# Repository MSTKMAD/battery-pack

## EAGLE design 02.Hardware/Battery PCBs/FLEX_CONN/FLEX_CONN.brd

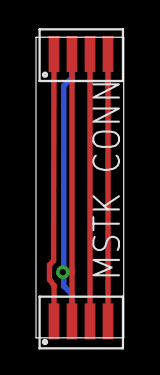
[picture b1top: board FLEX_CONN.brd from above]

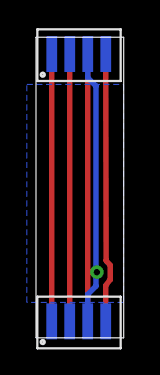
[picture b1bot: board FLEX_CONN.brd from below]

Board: 2 copper layers, 4.9 x 16.7 mm, 4 parts (2 on the bottom side), 4 nets.

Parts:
U$1, U$2, U$3, U$4: FLEX4

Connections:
GND: U$1.2, U$2.2, U$3.3, U$4.3
unnamed: U$1.1, U$2.1
unnamed: U$1.3, U$2.3
unnamed: U$1.4, U$2.4

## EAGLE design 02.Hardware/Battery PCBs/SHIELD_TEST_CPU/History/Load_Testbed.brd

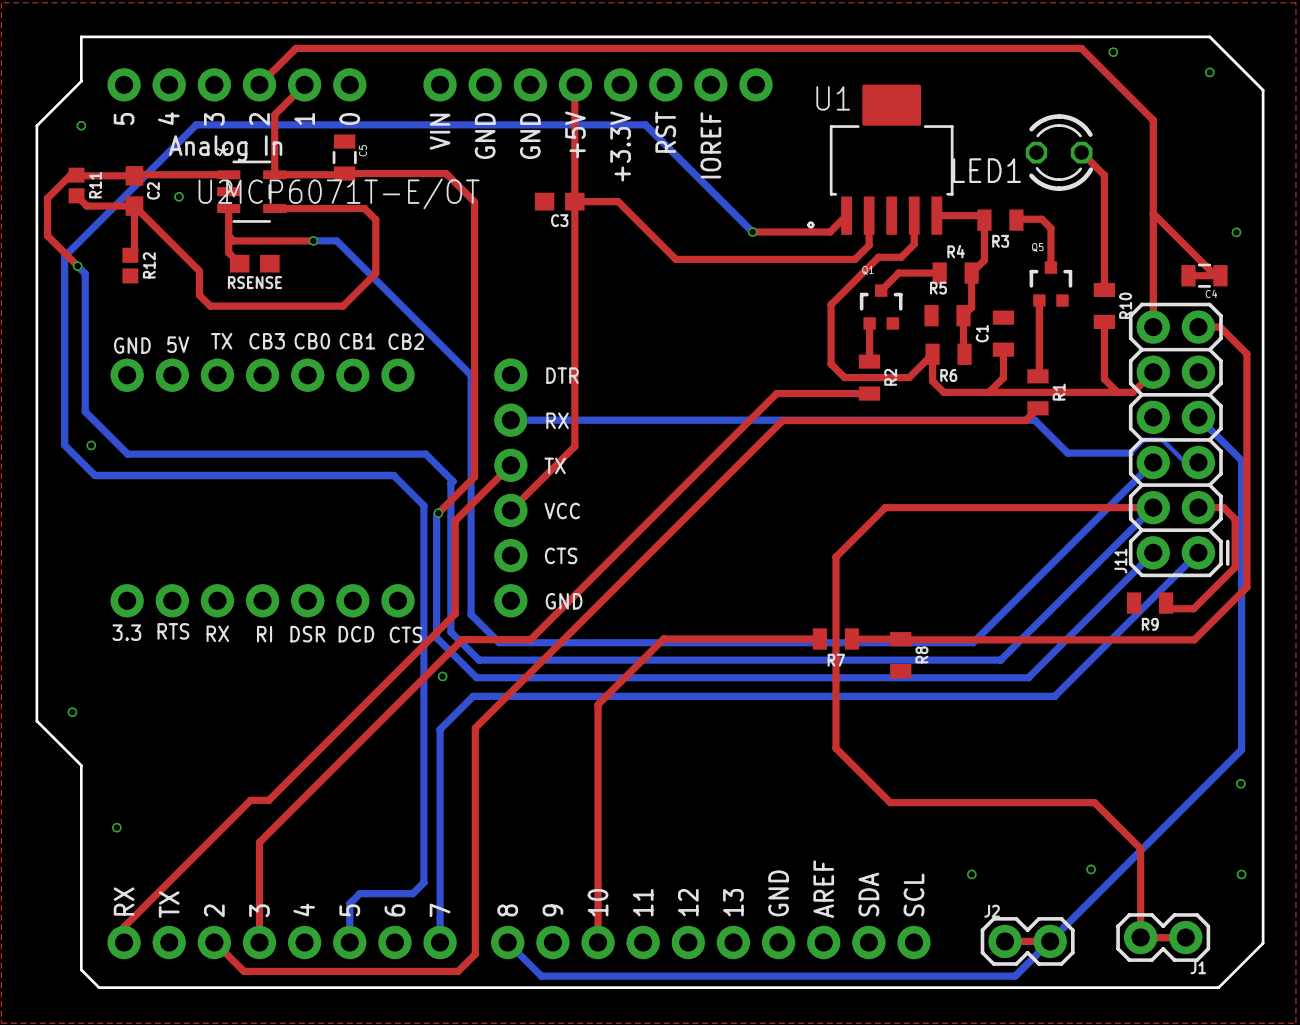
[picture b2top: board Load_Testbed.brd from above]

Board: 4 copper layers, 69.0 x 53.5 mm, 30 parts (0 on the bottom side), 24 nets.

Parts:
C1: 1.0uF; 0805
C2: 0.1uF; 0603
C3: 4.7uF; 0603
C4, C5: 100n; 0805
J1, J2: 1X02
J11: 2X6 FEMALE; 2X6
JP1: 1X06_NO_SILK
JP5, JP6: 1X07_NO_SILK
LED1: LED3MM
Q1, Q5: 2N7002PW; SOT323
R1, R2, R3, R4, R5, R6, R7, R8, R9, R10: 0805
R11: 15k; 0402
R12: 1k; 0402
RSENSE: 10mR; 0603
U1: MCP1825T-ADJE/DCSOT-223_5MC_MCH-M; SOT-223_5MC_MCH-M
U2: MCP6071T-E/OT; SOT-23-5_MC_MCH
U$4: ARDUINO_R3_SHIELD; UNO_R3_SHIELD

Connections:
ENABLE_LDO: U1.1, U$4.D5
GND: C1.2, C3.2, C4.1, C5.1, J2.1, J2.2, JP1.1, LED1.K, Q1.2, Q5.2, R5.1, R8.2, R9.2, R12.2, RSENSE.1, U1.3, U2.2, U$4.AREF, U$4.GND@0, U$4.GND@1, U$4.GND@2
ISENSE_RAW: J11.11, R7.1, R8.1
unnamed: C2.2, R11.2, R12.1, U2.4
unnamed: Q5.1, R1.1
unnamed: Q1.1, R2.1
unnamed: Q5.3, R3.1
unnamed: Q1.3, R4.1
unnamed: LED1.A, R10.1
unnamed: R3.2, R4.2, R5.2, R6.1, U1.5
unnamed: R7.2, U$4.D10
SCA_2: J11.1, U$4.D7
SCL_2: J11.7, U$4.D8
SW1: R1.2, U$4.D2
SW2: R2.2, U$4.D3
TST_MODE: J11.3, R9.1
TX0: J11.5, JP1.5
TX_FTDI: JP1.4, U$4.RX
VBUS+: C1.1, J11.10, R6.2, R10.2, U1.4
VBUS-: J11.6, RSENSE.2, U2.3
VCC: C5.2, J11.2, U2.5, U$4.A1
VCC-ISO: C3.1, JP1.3, U1.2, U$4.5V
VCC_2: C4.2, J11.12, U$4.A2
VOUTSENSE: C2.1, J1.1, J1.2, J11.4, R11.1, U2.1

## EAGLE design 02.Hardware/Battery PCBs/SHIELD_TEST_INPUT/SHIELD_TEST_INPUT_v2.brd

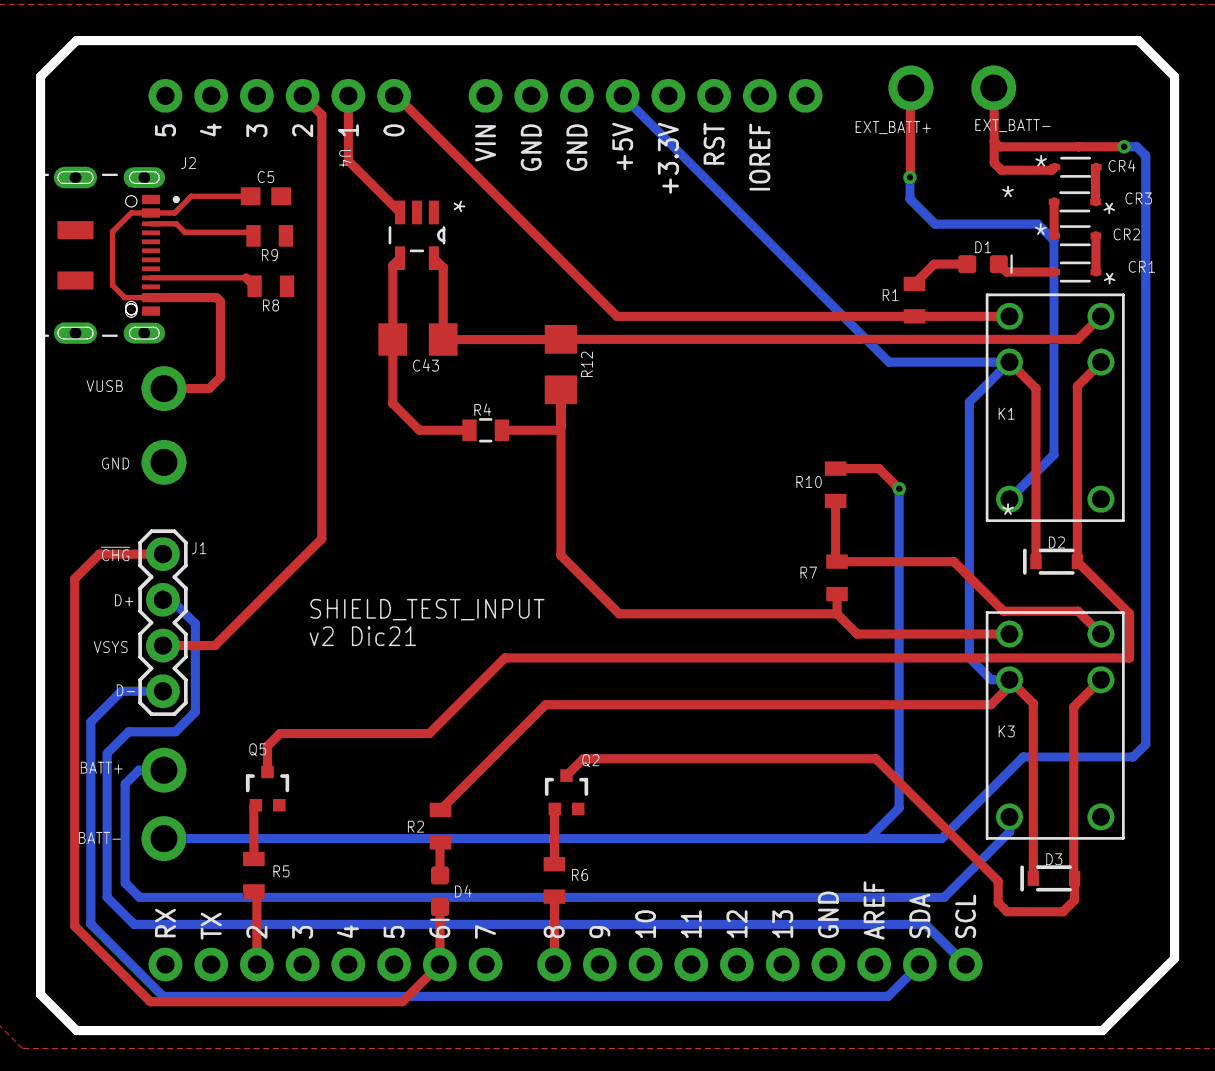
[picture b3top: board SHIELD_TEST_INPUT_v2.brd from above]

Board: 2 copper layers, 63.0 x 55.0 mm, 30 parts (0 on the bottom side), 28 nets.

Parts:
B1: ARDUINO_UNO_R3_SHIELDBASIC; UNO_R3_SHIELD
BATT+: TEST-POINT2; PAD.02X.02
BATT-: TEST-POINT2; PAD.02X.02
C5: 0.1uF; 0603
C43: 10uF; 1206
CR1, CR2, CR3, CR4: 1N4148WSF-7; SOD323F_DIO
D1, D4: LED-0603
D2, D3: 250mA/100V; SOD-323
J1: 1X04
J2: DX07S016JA1R1500; JAE_DX07S016JA1R1500
K1, K3: G5V-1-T90_DC5; RELAY_G5V-1_OMR
Q2, Q5: 2N7002PW; SOT323
R1: 100; 0805
R2: 1k5; 0805
R4: 10K; 0805
R5, R6: 330; 0805
R7, R10: 10k; 0805
R8, R9: 5k1; 0805
R12: 0.010; 1206
U4: MAX9938FEUK+T; SOT95P280X145-5N

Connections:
!CHG: B1.D6, D4.C, J1.4
BATT-: BATT-.P$1, CR4.1, R10.2
CC1: J2.3, R9.2
CC2: J2.9, R8.2
D+: B1.SDA, J1.1
D-: B1.SCL, J1.3
EXT_BATT+: BATT+.P$1, K1.5
EXT_BATT+1: K3.1, R4.2, R7.2, R12.2
GND: B1.GND@0, B1.GND@1, B1.GND@2, C5.2, J2.1, J2.12, J2.S1, J2.S2, J2.S3, J2.S4, J2.S5, J2.S6, Q2.2, Q5.1, Q5.2, R5.1, R8.1, R9.1, U4.1, U4.2
ISENSE: B1.A1, U4.3
LOW_OUTPUT: B1.D8, R6.2
unnamed: CR1.2, D1.C
unnamed: CR1.1, CR2.2
unnamed: D1.A, R1.2
unnamed: CR2.1, CR3.2
unnamed: D4.A, R2.1
unnamed: CR3.1, CR4.2
unnamed: D3.A, K3.9, Q2.3
unnamed: Q2.1, R6.1
unnamed: C43.2, R4.1, U4.4
unnamed: D2.A, K1.9, Q5.3
N&17: B1.A0, K1.1, R1.1
SWITCH: B1.D2, R5.2
VCC: B1.5V, D2.C, D3.C, K1.2, K3.2, R2.2
VO_TPS: C43.1, K1.10, R12.1, U4.5
VO_TPS1: K3.10, R7.1, R10.1
VSYS: B1.A2, J1.2
VUSB: C5.1, J2.2, J2.11

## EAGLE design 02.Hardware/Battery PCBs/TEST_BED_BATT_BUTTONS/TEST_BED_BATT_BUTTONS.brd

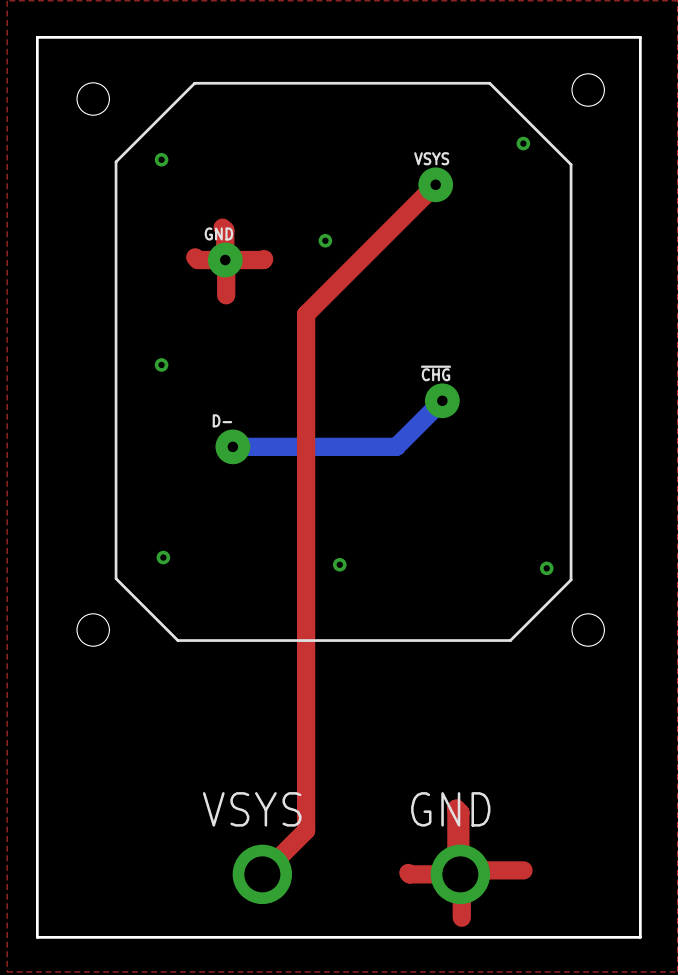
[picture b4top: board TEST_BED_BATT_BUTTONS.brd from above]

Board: 2 copper layers, 33.5 x 50.0 mm, 6 parts (0 on the bottom side), 3 nets.

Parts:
!CHG: 1X01_POGOPIN_HOLE_0.061_DIA
D-: 1X01_POGOPIN_HOLE_0.061_DIA
GND: 1X01_POGOPIN_HOLE_0.061_DIA
J1, J2: 1X01_2MM
VSYS: 1X01_POGOPIN_HOLE_0.061_DIA

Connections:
D-: !CHG.2, D-.2
GND: GND.2, J2.1
VSYS: J1.1, VSYS.2

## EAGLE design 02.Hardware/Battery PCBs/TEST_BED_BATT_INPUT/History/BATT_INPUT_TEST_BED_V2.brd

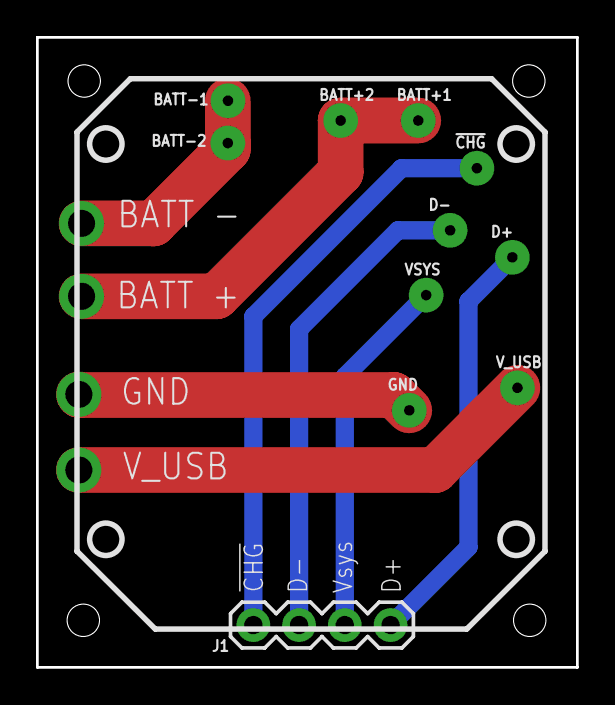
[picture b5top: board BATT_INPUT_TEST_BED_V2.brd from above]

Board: 2 copper layers, 30.0 x 35.0 mm, 11 parts (0 on the bottom side), 6 nets.

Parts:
!CHG!: 1X01_POGOPIN_HOLE_0.061_DIA
BATT+1, BATT+2: 1X01_POGOPIN_HOLE_0.061_DIA
BATT-1, BATT-2: 1X01_POGOPIN_HOLE_0.061_DIA
D+: 1X01_POGOPIN_HOLE_0.061_DIA
D-: 1X01_POGOPIN_HOLE_0.061_DIA
GND: 1X01_POGOPIN_HOLE_0.061_DIA
J1: FEMALE 2x3; 1X04
VSYS: 1X01_POGOPIN_HOLE_0.061_DIA
V_USB: 1X01_POGOPIN_HOLE_0.061_DIA

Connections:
BATT+: BATT-1.2, BATT-2.2
BATT-: BATT+1.2, BATT+2.2
unnamed: J1.3, VSYS.2
unnamed: D+.2, J1.4
unnamed: !CHG!.2, J1.1
unnamed: D-.2, J1.2

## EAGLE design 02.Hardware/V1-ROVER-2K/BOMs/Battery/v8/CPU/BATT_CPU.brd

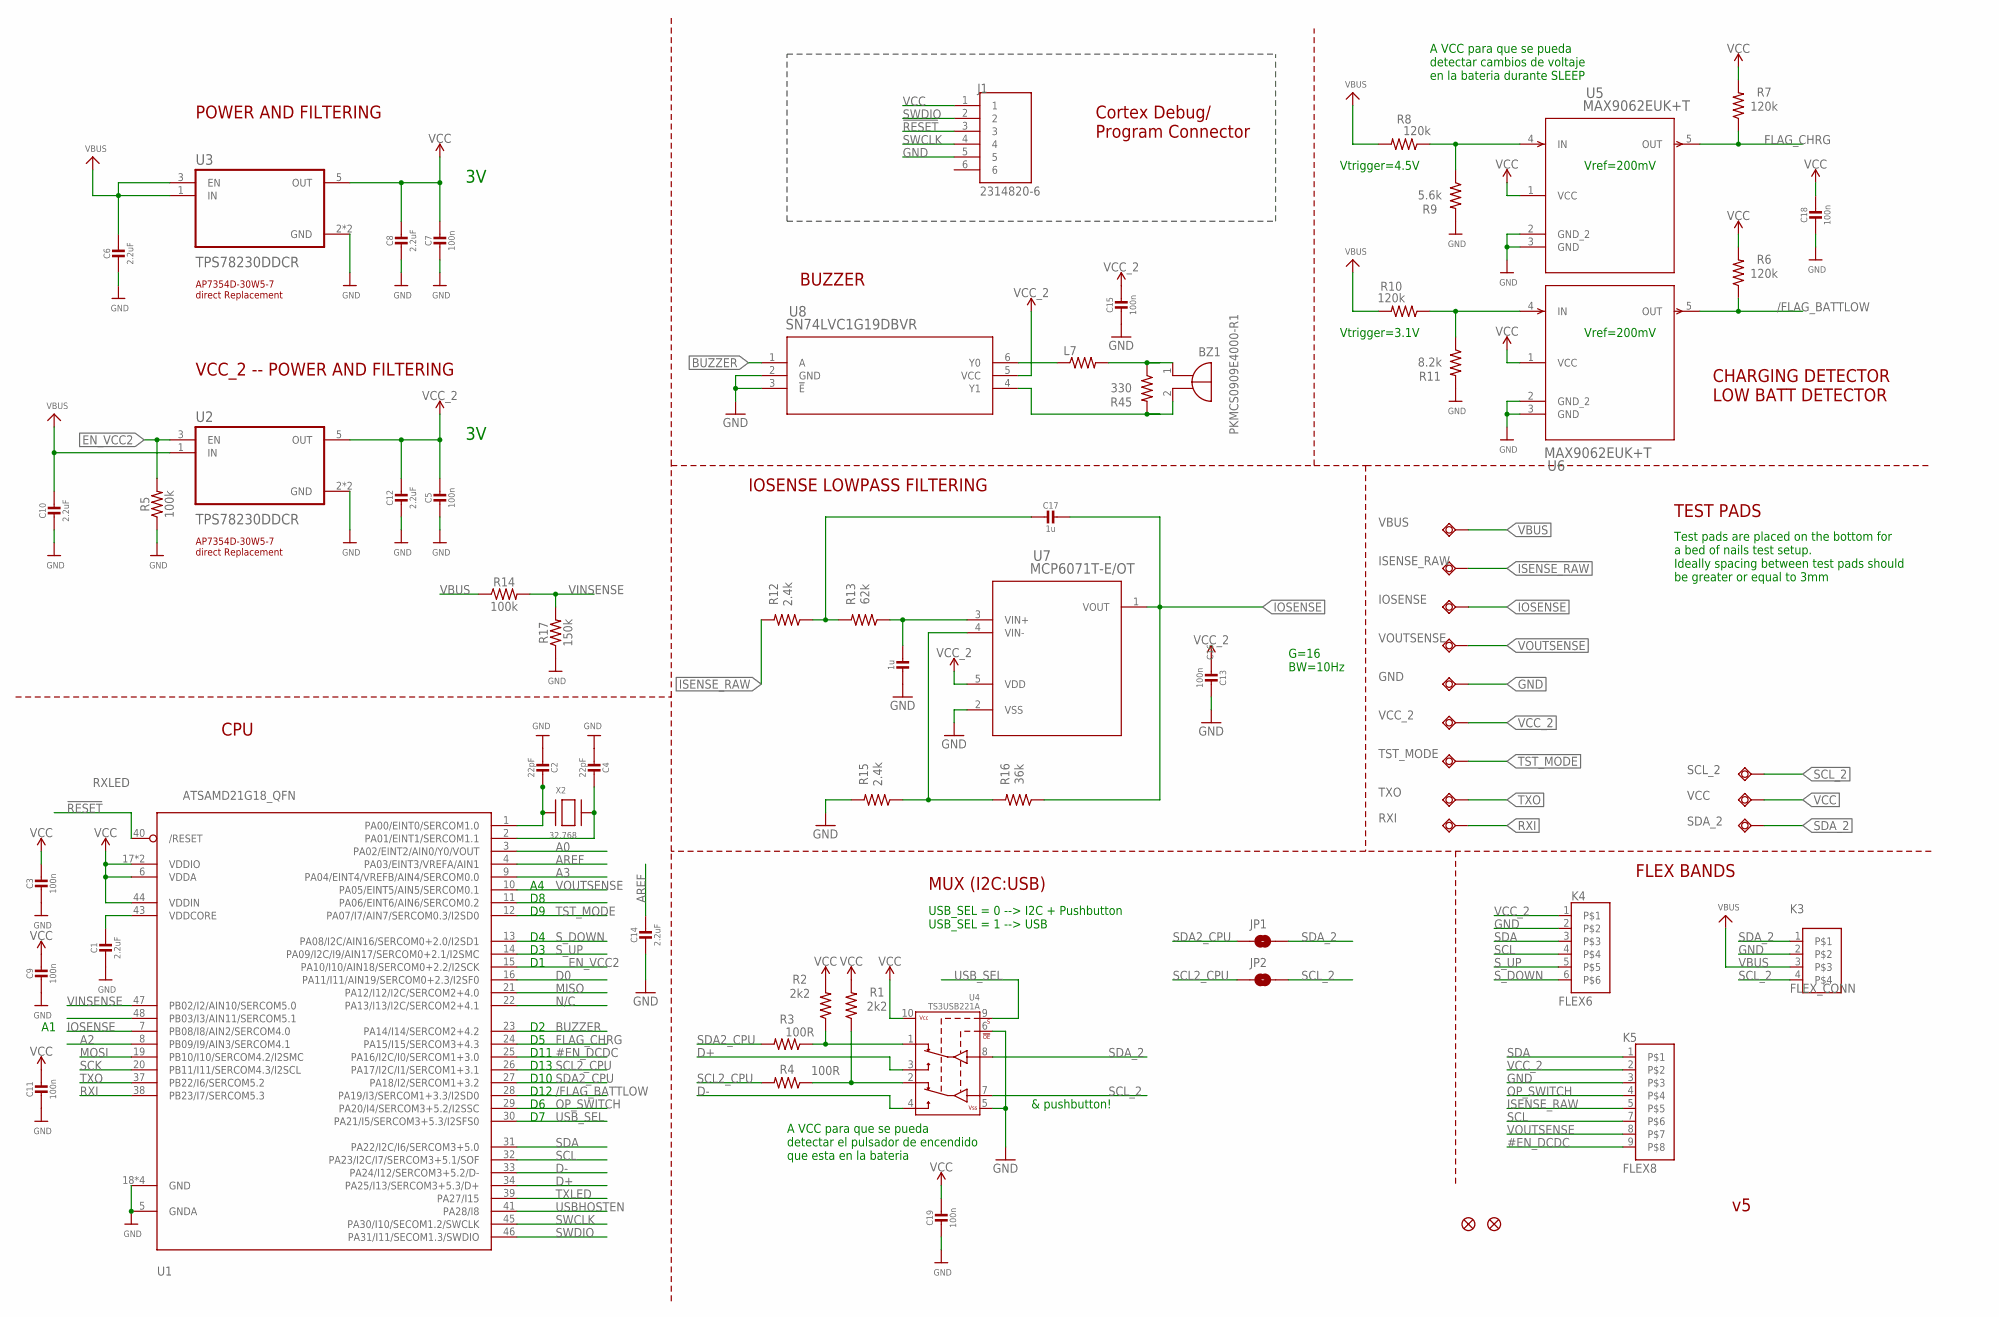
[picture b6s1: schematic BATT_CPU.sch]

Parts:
BZ1: PKMCS0909E4000-R1; PKMCS0909
C1, C14: 2.2uF; 0603-NO
C2, C4: 22pF; 0603-NO
C3, C5, C7, C9, C11, C13, C15, C18, C19: 100n; 0603-NO
C6, C8, C10, C12: 2.2uF; 0805-NO
C16, C17: 1u; 0603-NO
GND: TESTPAD_TPSQB1,27; TESTPAD_B1,27
IOSENSE: TESTPAD_TPSQB1,27; TESTPAD_B1,27
ISENSE_RAW: TESTPAD_TPSQB1,27; TESTPAD_B1,27
J1: 2314820-6; TE_2314820-6
JP1, JP2: JUMPER-SMT_2_NO_SILK; SMT-JUMPER_2_NO_SILK
K3: FLEX_CONN; FLEX4
K4: FLEX6
K5: FLEX8
L7: MMZ2012Y202BT000; 0805
R1, R2: 2k2; 0603
R3, R4: 100R; 0603
R5, R14: 100k; 0603
R6, R7, R8, R10: 120k; 0603
R9: 5.6k; 0603
R11: 8.2k; 0603
R12, R15: 2.4k; 0603
R13: 62k; 0603
R16: 36k; 0603
R17: 150k; 0603
R45: 330; 0603
RXI: TESTPAD_TPSQB1,27; TESTPAD_B1,27
SCL_2: TESTPAD_TPSQB1,27; TESTPAD_B1,27
SDA_2: TESTPAD_TPSQB1,27; TESTPAD_B1,27
TST_MODE: TESTPAD_TPSQB1,27; TESTPAD_B1,27
TXO: TESTPAD_TPSQB1,27; TESTPAD_B1,27
U1: ATSAMD21G18_QFN; TQFN48_7MM
U2, U3: TPS78230DDCR; SOT95P280X110-5N
U4: TS3USB221A; QFN-10-RSE
U5, U6: MAX9062EUK+T; 21-0057F_MXM
U7: MCP6071T-E/OT; SOT-23-5_MC_MCH
U8: SN74LVC1G19DBVR; DBV6
U$34, U$35: FIDUCIAL""; FIDUCIAL_1MM
VBUS: TESTPAD_TPSQB1,27; TESTPAD_B1,27
VCC: TESTPAD_TPSQB1,27; TESTPAD_B1,27
VCC_2: TESTPAD_TPSQB1,27; TESTPAD_B1,27
VOUTSENSE: TESTPAD_TPSQB1,27; TESTPAD_B1,27
X2: 32.768; XTAL3215

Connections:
!RESET: J1.3, U1.40 (/RESET)
#EN_DCDC: K5.9, U1.25 (PA16/I2C/I0/SERCOM1+3.0)
/FLAG_BATTLOW: R6.1, U1.28 (PA19/I3/SERCOM1+3.3/I2SD0), U6.5 (OUT)
A0: U1.3 (PA02/EINT2/AIN0/Y0/VOUT)
A2: U1.8 (PB09/I9/AIN3/SERCOM4.1)
A3: U1.9 (PA04/EINT4/VREFB/AIN4/SERCOM0.0)
AREF: C14.1, U1.4 (PA03/EINT3/VREFA/AIN1)
BUZZER: U1.23 (PA14/I14/SERCOM2+4.2), U8.1 (A)
D0: U1.16 (PA11/I11/AIN19/SERCOM0+2.3/I2SF0)
D+: U1.34 (PA25/I13/SERCOM3+5.3/D+), U4.3 (2D+)
D-: U1.33 (PA24/I12/SERCOM3+5.2/D-), U4.4 (2D-)
EN_VCC2: R5.2, U1.15 (PA10/I10/AIN18/SERCOM0+2.2/I2SCK), U2.3 (EN)
FLAG_CHRG: R7.1, U1.24 (PA15/I15/SERCOM3+4.3), U5.5 (OUT)
GND: C1.2, C2.2, C3.2, C4.2, C5.2, C6.2, C7.2, C8.2, C9.2, C10.2, C11.2, C12.2, C13.2, C14.2, C15.2, C16.2, C18.2, C19.2, GND.TP, J1.5, K3.2, K4.2, K5.3, R5.1, R9.2, R11.2, R15.2, R17.1, U1.5 (GNDA), U1.18 (GND), U1.35 (GND), U1.42 (GND), U1.THERMAL (GND), U2.2 (GND), U2.4 (GND), U3.2 (GND), U3.4 (GND), U4.5 (VSS), U4.6 (!OE), U5.2 (GND_2), U5.3 (GND), U6.2 (GND_2), U6.3 (GND), U7.2 (VSS), U8.2 (GND), U8.3 (!E)
IOSENSE: C17.2, IOSENSE.TP, R16.1, U1.7 (PB08/I8/AIN2/SERCOM4.0), U7.1 (VOUT)
ISENSE_RAW: ISENSE_RAW.TP, K5.5, R12.2
MISO: U1.21 (PA12/I12/I2C/SERCOM2+4.0)
MOSI: U1.19 (PB10/I10/SERCOM4.2/I2SMC)
unnamed: R15.1, R16.2, U7.4 (VIN-)
unnamed: R2.1, R3.1, U4.1 (1D+)
unnamed: R1.1, R4.1, U4.2 (1D-)
unnamed: C2.1, U1.1 (PA00/EINT0/SERCOM1.0), X2.P$1
unnamed: C4.1, U1.2 (PA01/EINT1/SERCOM1.1), X2.P$2
unnamed: C17.1, R12.1, R13.2
unnamed: R10.1, R11.1, U6.4 (IN)
unnamed: R8.1, R9.1, U5.4 (IN)
unnamed: C16.1, R13.1, U7.3 (VIN+)
unnamed: L7.1, U8.6 (Y0)
unnamed: BZ1.1 (+), L7.2, R45.1
unnamed: BZ1.2 (-), R45.2, U8.4 (Y1)
OP_SWITCH: K5.4, U1.29 (PA20/I4/SERCOM3+5.2/I2SSC)
RXI: RXI.TP, U1.38 (PB23/I7/SERCOM5.3)
SCK: U1.20 (PB11/I11/SERCOM4.3/I2SCL)
SCL: K4.4, K5.7, U1.32 (PA23/I2C/I7/SERCOM3+5.1/SOF)
SCL2_CPU: JP2.1, R4.2, U1.26 (PA17/I2C/I1/SERCOM1+3.1)
SCL_2: JP2.2, K3.4, SCL_2.TP, U4.7 (D-)
SDA: K4.3, K5.1, U1.31 (PA22/I2C/I6/SERCOM3+5.0)
SDA2_CPU: JP1.1, R3.2, U1.27 (PA18/I2/SERCOM1+3.2)
SDA_2: JP1.2, K3.1, SDA_2.TP, U4.8 (D+)
SWCLK: J1.4, U1.45 (PA30/I10/SECOM1.2/SWCLK)
SWDIO: J1.2, U1.46 (PA31/I11/SECOM1.3/SWDIO)
S_DOWN: K4.6, U1.13 (PA08/I2C/AIN16/SERCOM0+2.0/I2SD1)
S_UP: K4.5, U1.14 (PA09/I2C/I9/AIN17/SERCOM0+2.1/I2SMC)
TST_MODE: TST_MODE.TP, U1.12 (PA07/I7/AIN7/SERCOM0.3/I2SD0)
TXO: TXO.TP, U1.37 (PB22/I6/SERCOM5.2)
USB_SEL: U1.30 (PA21/I5/SERCOM3+5.3/I2SFS0), U4.9 (S)
VBUS: C6.1, C10.1, K3.3, R8.2, R10.2, R14.1, U2.1 (IN), U3.1 (IN), U3.3 (EN), VBUS.TP
VCC: C3.1, C7.1, C8.1, C9.1, C11.1, C18.1, C19.1, J1.1, R1.2, R2.2, R6.2, R7.2, U1.6 (VDDA), U1.17 (VDDIO), U1.36 (VDDIO), U1.44 (VDDIN), U3.5 (OUT), U4.10 (VCC), U5.1 (VCC), U6.1 (VCC), VCC.TP
VCC_2: C5.1, C12.1, C13.1, C15.1, K4.1, K5.2, U2.5 (OUT), U7.5 (VDD), U8.5 (VCC), VCC_2.TP
VDDCORE: C1.1, U1.43 (VDDCORE)
VINSENSE: R14.2, R17.2, U1.47 (PB02/I2/AIN10/SERCOM5.0)
VOUTSENSE: K5.8, U1.10 (PA05/EINT5/AIN5/SERCOM0.1), VOUTSENSE.TP

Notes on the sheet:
POWER AND FILTERING
N/C
TXLED
USBHOSTEN
RXLED
Cortex Debug/ Program Connector
BUZZER
AP7354D-30W5-7 direct Replacement
VCC_2 -- POWER AND FILTERING
A VCC para que se pueda detectar el pulsador de encendido que esta en la bateria
D10
A VCC para que se pueda detectar cambios de voltaje en la bateria durante SLEEP
G=16 BW=10Hz
IOSENSE LOWPASS FILTERING
FLEX BANDS
MUX (I2C:USB)
CHARGING DETECTOR LOW BATT DETECTOR
CPU
Vref=200mV
Vtrigger=4.5V
Vtrigger=3.1V
D13
D11
USB_SEL = 0 --> I2C + Pushbutton USB_SEL = 1 --> USB
& pushbutton!
D12
TEST PADS
Test pads are placed on the bottom for a bed of nails test setup. Ideally spacing between test pads should be greater or equal to 3mm

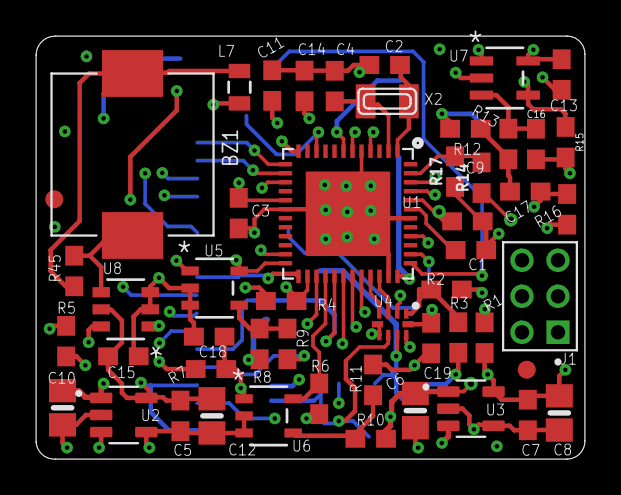
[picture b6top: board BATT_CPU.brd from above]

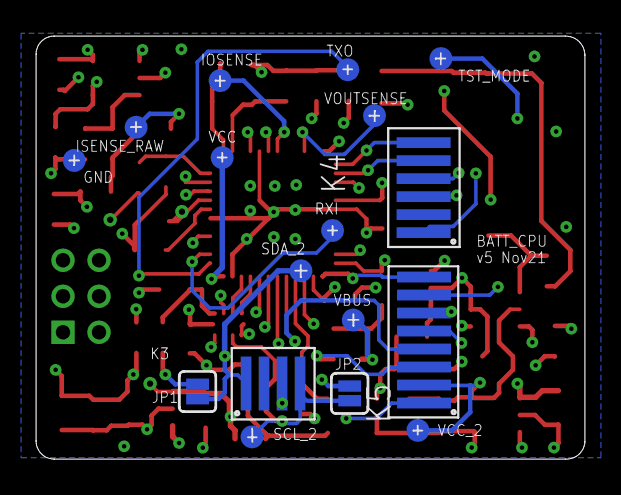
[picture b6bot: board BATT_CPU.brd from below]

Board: 4 copper layers, 30.5 x 23.5 mm, 68 parts (17 on the bottom side), 45 nets.

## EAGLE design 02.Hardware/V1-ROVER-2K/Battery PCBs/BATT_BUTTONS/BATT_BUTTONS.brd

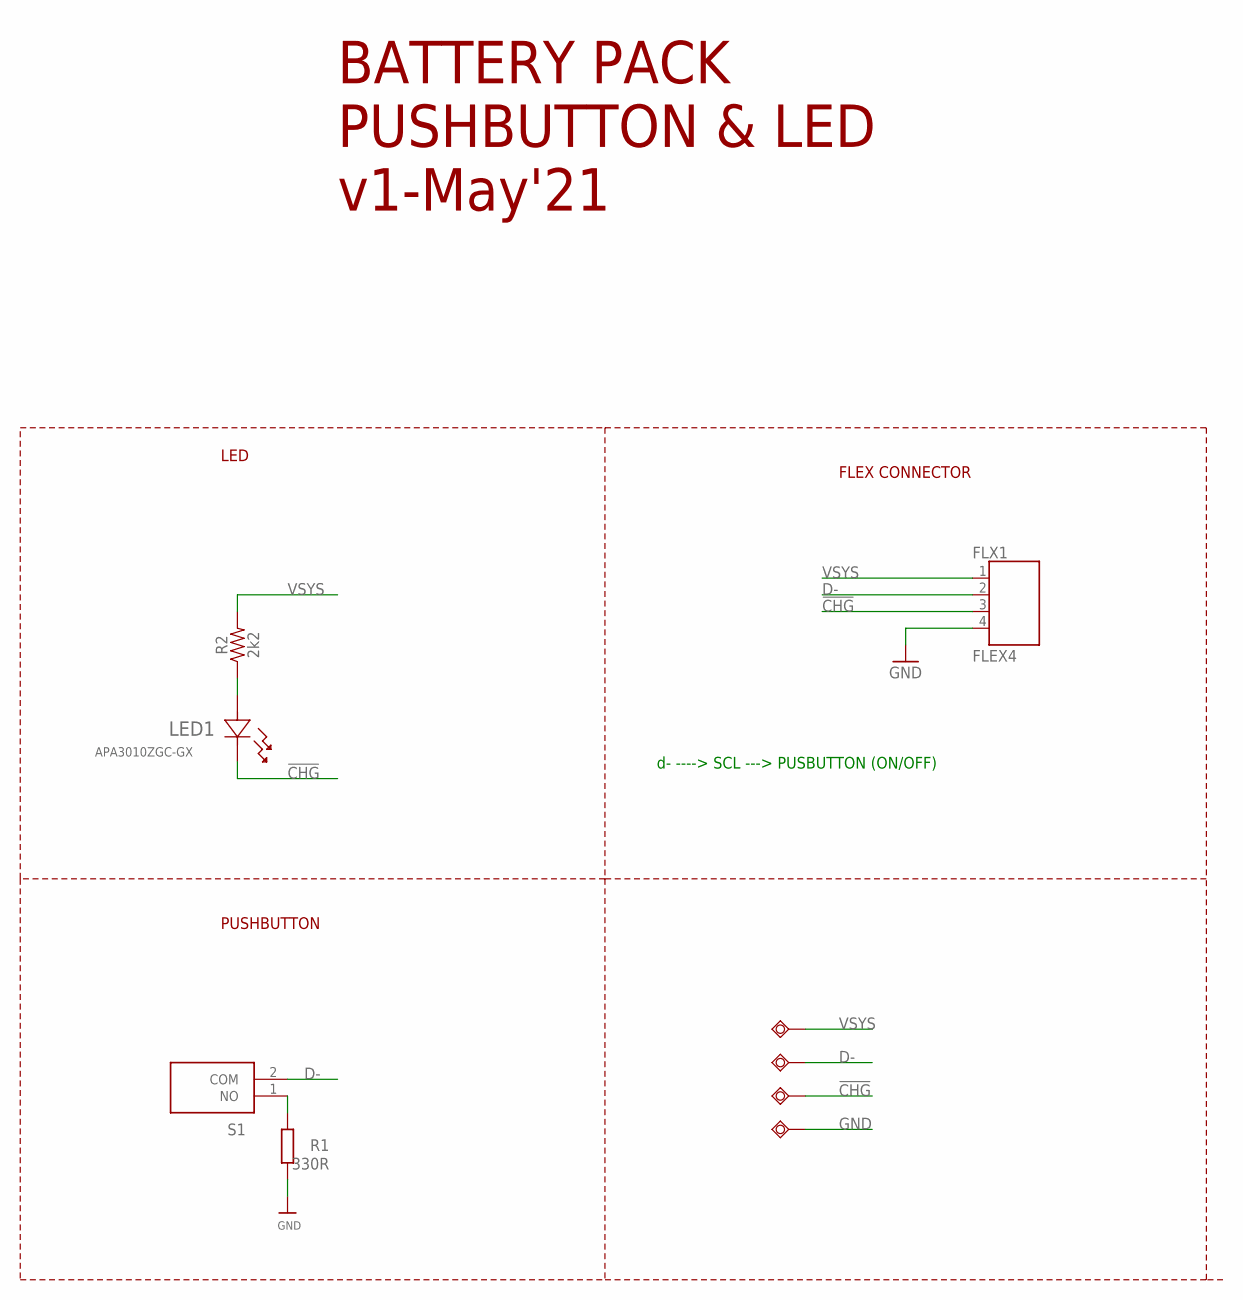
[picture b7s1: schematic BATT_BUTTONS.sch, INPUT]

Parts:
!CHG: TESTPAD_TPSQB1,27; TESTPAD_B1,27
D-: TESTPAD_TPSQB1,27; TESTPAD_B1,27
FLX1: FLEX4
GND: TESTPAD_TPSQB1,27; TESTPAD_B1,27
LED1: APA3010ZGC-GX; LED_APA3010SRCPRV-GX_KNB
R1: 330R; R0603
R2: 2k2; 0402
S1: KXT311LHS
VSYS: TESTPAD_TPSQB1,27; TESTPAD_B1,27

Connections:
!CHG!: !CHG.TP, FLX1.3, LED1.1
D-: D-.TP, FLX1.2, S1.2 (COM)
GND: FLX1.4, GND.TP, R1.1
unnamed: R1.2, S1.1 (NO)
unnamed: LED1.2, R2.1
VSYS: FLX1.1, R2.2, VSYS.TP

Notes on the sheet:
BATTERY PACK PUSHBUTTON & LED v1-May'21
LED
d- ----> SCL ---> PUSBUTTON (ON/OFF)
FLEX CONNECTOR
PUSHBUTTON

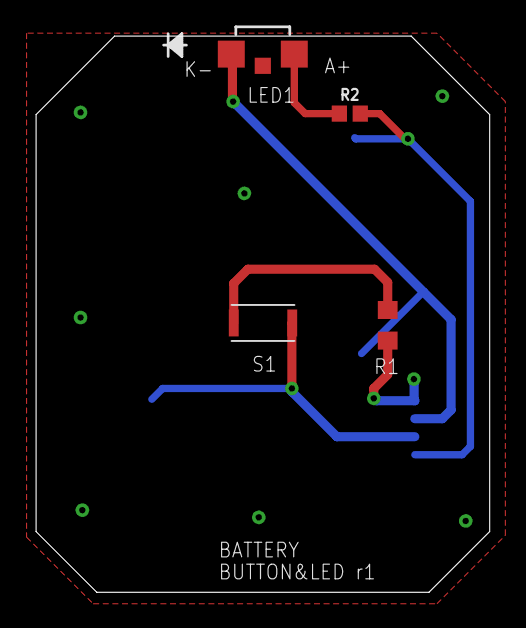
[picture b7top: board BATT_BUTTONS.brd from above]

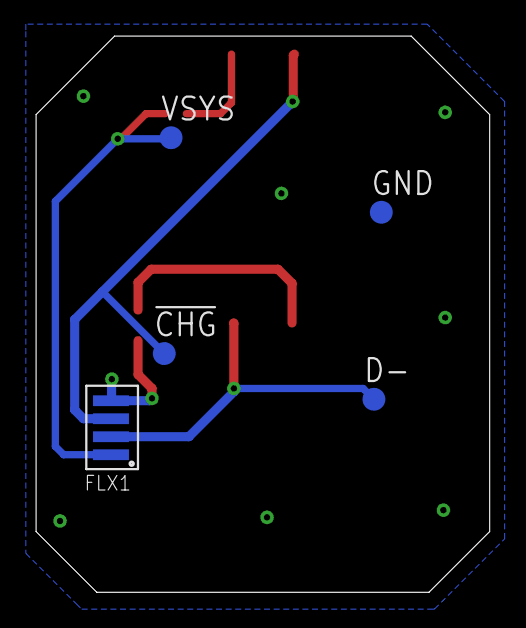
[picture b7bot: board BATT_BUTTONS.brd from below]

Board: 2 copper layers, 25.2 x 30.9 mm, 9 parts (5 on the bottom side), 6 nets.

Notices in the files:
parts and their libraries:
SparkFun-Aesthetics: Licensing: Creative Commons ShareAlike 4.0 International - https://creativecommons.org/licenses/by-sa/4.0
microbuilder: This work is placed in the public domain, and may be freely used for commercial and non-commercial work with the following conditions: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
